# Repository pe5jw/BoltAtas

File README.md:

# BoltATAS

Netwerkcontroller voor de Yaesu **ATAS-100** motorantenne op de FT-897D, op basis van een **WT32-ETH01** (ESP32 + Ethernet).
Meet vooruit- en reflectievermogen (tandem match + 2× AD8307), stuurt de antennemotor via de DC-spanning op de coax
en stemt zelfstandig af op de laagste SWR. Bediening via een HTTP API in BoltSwitch-stijl, of met de knoppen UP, DOWN en TUNE op de print. Drie LED's (groen, oranje, rood) tonen de SWR.

PE5JW — hardware v1.3, firmware v1.2 (2026-11-25)

> **Status:** ontwerp en firmware zijn met tools gecontroleerd, maar er is nog **niets gebouwd of op de band getest**.
> - Schema: één doorverbonden tekening met echte draden. De netlist is door KiCad zelf geëxporteerd en vergeleken met de bedoelde verbindingen (266 pinnen, 60 netten, 0 fouten). Daarbij zijn de pin-types gecontroleerd.
> - PCB: gegenereerd uit dit schema en eraan gekoppeld. DRC geeft 0 fouten en 0 onverbonden pads; er blijven 2 cosmetische silkscreen-waarschuwingen over (WT32-footprint).
> - Firmware: de afstemlogica is getest in een simulatie (9000 runs). De Ethernet/WiFi-wisseling en het frontpaneel (knoppen en SWR-LED's) zijn getest met de echte sketch tegen stubs voor arduino-esp32 core 2.x en 3.x. Met de echte ESP32-toolchain is de sketch hier niet gecompileerd.
>
> Zie [Open punten](#open-punten) voor wat je bij de bouw moet nameten.

## Mappen

| Map | Inhoud |
|---|---|
| `hardware/` | KiCad 7 project: `BoltATAS.kicad_sch`, `.kicad_pcb`, `.kicad_pro`, `.kicad_dru`, projectbibliotheek (`BoltATAS.kicad_sym`, `BoltATAS.pretty/`) |
| `hardware/fab/` | Gerbers + boorbestanden (`BoltATAS-gerbers.zip`), BOM (`BoltATAS-BOM.csv`), bestellijst voor DigiKey (`BoltATAS-BOM-DigiKey.csv`, te uploaden in de BOM Manager), pick&place |
| `hardware/tools/` | Python-generators voor bibliotheek, schema en PCB, netlist-check, DRC, fab-uitvoer (`fab.py`), `build_all.sh` |
| `firmware/BoltATAS/` | Arduino sketch (`BoltATAS.ino`) + platformonafhankelijke logica (`AtasCore.h`) |
| `firmware/test/` | Simulatie van autotune/motor en test van de netwerkwisseling (draait op een PC) |
| `docs/` | Schema als PDF/PNG, PCB-renders, DRC-rapport |

## Hardware

```
FT-897D ─ J1 ─ T1 (stroomtrafo) ─ RF_LINE ─ C1..C3 (DC-blok) ─ RF_ANT ─ J2 ─ ATAS-100
                    │                  │                          │
               FWD_PORT ── T2 (spanningstrafo, 30T naar GND)      L1 RF-choke
                    │      1T tussen FWD_PORT en REF_PORT          │
             13 dB pad → AD8307 → IO36            COAX_DC ← R40 0.1 Ω ← K1/K2 relais ← 12 V / 8 V
             REF: 13 dB pad → AD8307 → IO39             INA180 → IO35 (motorstroom)
```

- **Tandem match** (Sontheimer): twee FT114-43 kernen, 1:30. T1 = stroomtrafo (1 winding = coax-ziel RF_TX→RF_LINE, 30 wdg van GND naar FWD_PORT). T2 = spanningstrafo (30 wdg van RF_LINE naar GND, 1 winding = coax-ziel tussen FWD_PORT en REF_PORT).
- **Koppeling** 29,5 dB + 13 dB π-pad = 42,5 dB. 120 W geeft +8,3 dBm op de AD8307 (lineair tot +16 dBm) en 2,31 V op de ADC; 200 W geeft 2,36 V (ESP32 lineair tot 2,45 V).
- **DC-blok** C1..C3 (3× 100 nF X7R 100 V) ligt tussen koppelaar en bias-tee. Er komt dus geen 8/12 V op de zender, en ook niet op T2 (diens 30 wdg zijn voor DC een kortsluiting).
- **Bias-tee** L1: 20 wdg 0,8 mm CuL op FT114-43 (≈240 µH).
- **Motor:** K1 (12 V = langer = frequentie omlaag) en K2 (8 V = korter = frequentie omhoog). Het NC-contact van K1 voedt de COM van K2, zodat 8 V en 12 V elkaar nooit kunnen raken. In rust ligt de lijn via R41 op 0 V.
- **Motorstroom:** 0,1 Ω + INA180A1 (2 mV/mA) op IO35. Daarmee detecteert de firmware kortsluiting (> 900 mA) en een open lijn (< 10 mA).
- **Frontpaneel** (blok F in het schema, onderrand van de print): knoppen UP, DOWN en TUNE, SWR-LED's groen/oranje/rood, de status-LED en de twee motor-LED's.
  - Knoppen schakelen naar GND, met 10k pull-up en 100 nF (1 ms ontdendering) en 1k in serie naar de GPIO.
  - J5 (1×8) is optioneel, voor knoppen en LED's in een frontplaat: 1 GND, 2 TUNE, 3 DOWN, 4 UP, 5 SWR rood, 6 SWR oranje, 7 SWR groen, 8 STATUS. De knoppen staan parallel aan die op de print. De LED-pinnen zitten ná de serieweerstand: monteer een LED óf op de print óf in de frontplaat, niet allebei.
- **Voeding:** 13,8 V → PTC 1,5 A → SS34 (ompoolbeveiliging) → TVS.
  - LM2940CT-12: low-dropout, want een LM7812 valt bij 13,3 V uit regeling.
  - LM7808.
  - Traco TSR 1-2450: een schakelende 5 V; een LM7805 is pin-compatibel, maar heeft dan een koelplaat nodig.

### Pinnen WT32-ETH01

| GPIO | Functie |
|---|---|
| IO36 | ADC FWD (AD8307 U4) |
| IO39 | ADC REF (AD8307 U5) |
| IO35 | ADC motorstroom |
| IO4 | K1, 12 V, antenne langer |
| IO32 | K2, 8 V, antenne korter |
| IO33 | status-LED |
| IO2 | SWR-LED groen |
| IO12 | SWR-LED oranje |
| IO14 | SWR-LED rood |
| IO15 | knop UP |
| IO5 | knop DOWN |
| IO17 | knop TUNE |
| IO0 | Ethernet-klok (50 MHz). Alleen via R50 naar BOOT-knop/header |

Ethernet gebruikt IO0, 16, 18, 19, 21–23 en 25–27. Daarmee zijn alle vrije GPIO's van de WT32-ETH01 in gebruik.

IO2, IO12, IO5 en IO15 zijn strapping-pinnen. Ze zitten daarom op plekken waar ze het opstarten niet storen:
- IO2 en IO12 sturen een LED naar GND, die houdt ze laag tijdens het booten. IO12 hoog bij het booten zou de flash op 1,8 V zetten.
- IO5 en IO15 zijn ingangen met pull-up; hoog is hun standaardniveau.
- In v1.0 stuurde IO5 een relais aan, dat tijdens het booten kon schakelen. Als knopingang is dat geen probleem.

**Programmeerheader J4** (USB-serieel, 3,3 V): 1 EN, 2 TX, 3 RX, 4 IO0 (via R50), 5 3V3 (alleen referentie, niet voeden), 6 GND. SW2 = RESET, SW1 = BOOT.

### Bouwnotities

1. **Toroids T1/T2:** elke kern staat rechtop in een sleuf in de print, met een stukje RG-58/RG-400 (±60 mm) er recht doorheen.
   - Ziel aan pad A en B. Mantel **aan één kant** solderen (pad SH, kant A); aan de andere kant de mantel afknippen.
   - T2 krijgt de volle lijnspanning: wikkel de 30 windingen met PTFE- of dubbel gelakt draad.
   - De kernen steken ±12 mm onder de print uit, dus gebruik afstandsbussen van ≥ 15 mm.
2. **FWD en REF verwisseld?** Draai de twee draden van de 30 windingen van T1 om.
3. **L1:** meet met een NanoVNA dat |Z| ≥ 1,5 kΩ is over 1,8–30 MHz. Haal je dat niet, voeg dan een tweede choke in serie toe.
4. **Relais:** de pinnummers volgen de KiCad SRD-footprint (1 COM, 3 NO, 4 NC). Controleer vóór het solderen met een multimeter dat COM–NC doorgang heeft.
5. **U1/U2** krijgen een klein koelplaatje, want ze voeren de motorstroom.
6. **WiFi:** de antenne van de WT32-ETH01 zit aan het eind tegenover de RJ45. Daaronder zit geen koper (keep-out). In een metalen kast werkt WiFi nauwelijks; gebruik dan Ethernet of een kunststof deksel.
7. Gerbers staan in `hardware/fab/BoltATAS-gerbers.zip`. Board: 150 × 114 mm, 2 lagen, 1,6 mm. De sleuven zitten in Edge.Cuts.
8. **Frontrij:** de knoppen en LED's staan op één lijn langs de onderrand. Monteer de print zo dat die rand achter de frontplaat zit, of gebruik J5 voor losse knoppen en LED's.

## Firmware

**Bouwen:** Arduino IDE of arduino-cli.
- Board: "WT32-ETH01 Ethernet Module" (of "ESP32 Dev Module").
- Core: arduino-esp32 2.0.x of 3.x.
- Bibliotheek: ArduinoJson 6.21+ of 7.x.

Kopieer `firmware/BoltATAS/secrets.h.example` naar `secrets.h` en vul de WiFi- en OTA-gegevens in.

**Netwerk** (één van beide, nooit allebei):
- Ethernet heeft voorrang.
- WiFi start pas als er na het opstarten 4 s geen kabel is, of 5 s nadat de kabel eruit is getrokken.
- Wordt een kabel ingeplugd, dan gaat WiFi direct uit (al bij link-up, nog vóór DHCP).
- Krijgt Ethernet 20 s lang geen DHCP-adres, dan valt de module terug op WiFi.
- Naam op het netwerk: mDNS `boltatas.local`. OTA-updates werken met wachtwoord.

**Frontpaneel:**
- **UP / DOWN:** de motor draait zolang je de knop vasthoudt (max. 15 s), met of zonder draaggolf. UP en DOWN tegelijk = stop.
- **TUNE:** start de autotune als er een draaggolf van 0,5–25 W is. Nog een keer drukken breekt af.
- Een knop die al ingedrukt is bij het opstarten telt pas na loslaten.
- **Boven 25 W beweegt de motor niet**, ook niet met de knoppen of `/up` en `/down`, omdat de contacten van de spriet dan kunnen vonken. Gaat het vermogen tijdens een handmatige beweging boven 25 W, dan stopt de motor.

**SWR-LED's:**

| LED | Betekenis |
|---|---|
| groen | SWR < 1,5 |
| oranje | SWR 1,5 – 2,5 |
| rood | SWR ≥ 2,5 |
| uit | geen draaggolf (≥ 0,5 W); blijft 0,4 s staan in SSB-pauzes |

De grenzen zijn in te stellen met `/cal?swr_green=1.5&swr_red=2.5`. Er zit 0,05 hysterese op, zodat een LED niet knippert op de grens. Tijdens het afstemmen tonen de LED's de actuele SWR.

De LED's knipperen ook 3× als terugmelding:
- groen: afstemmen gelukt
- oranje: beste resultaat, doel-SWR niet gehaald
- rood: afstemmen mislukt, of TUNE zonder draaggolf
- oranje + rood: vermogen te hoog (> 25 W)

Bij het opstarten branden alle drie kort (lamptest).

**Status-LED:**
- aan: Ethernet
- 1 Hz: WiFi
- 4 Hz: geen netwerk
- 8 Hz: aan het afstemmen
- dubbele flits: motorfout

### HTTP API

Alle verzoeken zijn GET en geven JSON terug, met CORS open.

| Endpoint | Functie |
|---|---|
| `/status` | SWR, FWD/REF in W en dBm, return loss, motorstroom, motorfout, tune-status, netwerk, SWR-LED (`swr_led`), knoppen (`buttons`) |
| `/up` `/down` | Motor draaien tot `/stop`, maximaal 15 s. Boven 25 W: fout 409 `power_too_high` |
| `/up?ms=N` `/down?ms=N` | Motor N ms laten draaien (10…15000) |
| `/stop` | Motor stoppen en lopende afstemming afbreken |
| `/tune` | Autotune starten. Vereist een draaggolf van 0,5–25 W |
| `/tune?target=1.5&dir=up` | Doel-SWR (1.1–3.0) en beginrichting. Gebruik `dir=up` als de frequentie omhoog ging |
| `/cal` | Kalibratie tonen |
| `/cal?fwd_w=10` | FWD-koppeling instellen op een bekend vooruitvermogen (dummy load + referentiemeter) |
| `/cal?ref_w=10` | REF-koppeling instellen: voed hiervoor RF in via de ANT-aansluiting |
| `/cal?travel_ms=45000` | Looptijd van de antenne van eindstop tot eindstop (zelf meten) |
| `/cal?swr_green=1.5&swr_red=2.5` | Grenzen van de SWR-LED's |

`/up` en `/down` breken een lopende autotune af.

**Autotune** werkt in twee fasen:
1. **Sweep:** de motor draait continu en de RF wordt elke 40 ms bemonsterd.
2. **Fijn zoeken:** stapsgewijs, met een halvering van de stapgrootte bij elke omkering. Daarna gaat de antenne terug naar de beste positie.

De firmware **weigert te tunen boven 25 W**, omdat het bewegen van de spriet onder vol vermogen de contacten kan doen vonken. Hij stopt ook bij verlies van RF en bij een motorfout.

## Tests

```bash
cd firmware/test
ARDUINOJSON_SRC=/pad/naar/ArduinoJson/src ./run_tests.sh
```

- **`sim_test`:**
  - RF-rekenwerk, de motor-interlock en de dode tijd tussen relais.
  - Autotune tegen een gesimuleerde ATAS-100, met willekeurige resonantie, startpositie, voetpuntweerstand, coaxverlies, motoruitloop en detectorruis.
  - 3 × 3000 runs: 0 gemist, 0 time-outs.
  - Gemiddeld 40 s zonder richtingshint en 13 s met hint.
- **`sim_test`** test ook het frontpaneel los: ontdendering (ook een knop die vastzit bij het opstarten), de knopacties, en de SWR-kleuren met hysterese, houdtijd en knipperen.
- **`net_test`:** draait de echte sketch tegen stubs met de API van core 2.x en 3.x.
  - Ethernet/WiFi-wisseling: geen kabel, inpluggen, uittrekken, geen DHCP en late DHCP.
  - Frontpaneel: lamptest, UP/DOWN zonder draaggolf, TUNE zonder draaggolf (geweigerd, rood knippert), groen/oranje/rood/uit bij 10 W, UP geweigerd bij 100 W, motor stopt als het vermogen tijdens een beweging boven 25 W komt, TUNE starten en afbreken.

## KiCad-bestanden opnieuw genereren

Het schema en de PCB worden gegenereerd uit `hardware/tools/`. Benodigd: KiCad 7 (`kicad-cli` en de pcbnew-Python-module), Java 25 en `freerouting-2.5.0.jar`.

```bash
FREEROUTING=/pad/freerouting-2.5.0.jar JAVA=java hardware/tools/build_all.sh
```

Dit draait de volgende stappen achter elkaar: bibliotheken → schema → netlist via KiCad → vergelijking met de bedoelde verbindingen → plaatsing → autorouter → GND-vlakken → DRC → Gerbers, BOM, pick&place en de afbeeldingen in `docs/`. Freerouting is niet deterministisch; het script probeert het routeren opnieuw (max. 8×) tot de DRC schoon is.

De footprints in de PCB zijn aan de schemasymbolen gekoppeld, dus **Tools → Update PCB from Schematic** (F8) in KiCad werkt gewoon. Handmatige aanpassingen in KiCad mogen, maar die worden bij een volgende generatorrun overschreven.

## Wijzigingen in v1.3 (hardware) / v1.2 (firmware)

- **Frontpaneel:** knoppen UP, DOWN en TUNE (SW3–SW5) en SWR-LED's groen/oranje/rood (LED4–LED6), met de status-LED en de motor-LED's samen op een rij langs de onderrand. J5 is optioneel, voor een losse frontplaat.
- Print 14 mm hoger: 150 × 114 mm.
- Firmware 1.2.0:
  - knoppen en SWR-LED's;
  - de motor beweegt niet meer boven 25 W, ook niet handmatig;
  - `/status` meldt de SWR-LED en de knoppen;
  - `/cal` heeft de SWR-grenzen erbij.

## Wijzigingen in v1.2

- **Schema opnieuw getekend als één geheel:** alle onderdelen zijn met draden verbonden, met junctions op de aftakkingen. Netlabels staan alleen nog op de belangrijke netten (RF_TX, RF_LINE, FWD_PORT, K1_CTRL, FWD_ADC, enz.) en niet meer op elke pin. Indeling: A RF-pad, B detectoren, C motor/relais, D voeding, E WT32-ETH01. De schakeling zelf is gelijk aan v1.1.
- **J4 PROG** heeft een logischere volgorde: 1 EN, 2 TX, 3 RX, 4 IO0, 5 3V3, 6 GND.
- **PCB opnieuw gegenereerd** uit het nieuwe schema, met de footprints gekoppeld aan de symbolen. Silkscreen opgeschoond: van 12 naar 2 waarschuwingen.
- De generators geven nu steeds dezelfde UUID's, zodat een nieuwe run geen onnodige git-diffs geeft.
- Nieuw: `hardware/tools/fab.py` voor Gerbers, BOM, pick&place en de afbeeldingen.

## Wijzigingen in v1.1 t.o.v. v1.0 (review)

v1.0 had geen bruikbare KiCad-bestanden: het schema bevatte geen draden of symbooldefinities, en de PCB had geen sporen, verkeerde footprints en overlappende onderdelen. De belangrijkste inhoudelijke fouten:

1. **Tandem match:** T2 zat in serie met de lijn in plaats van als spanningstrafo over de lijn. Daardoor was de koppelaar niet richtingsgevoelig en werkte de SWR-meting niet.
2. **DC-blok ontbrak:** de 8/12 V kwam op de antenne-uitgang van de FT-897D.
3. **AD8307 verkeerd aangesloten:**
   - OUT (pin 4) aan GND, ENB (pin 6) als uitgang gebruikt en INM DC aan massa.
   - De 4k7-load verlaagde de slope van 25 naar ±6,8 mV/dB.
   - Een condensator op OFS ontbrak; zonder die condensator ligt de hoogdoorlaatgrens op ±700 kHz.
4. **Overbelasting bij 120 W:** de detector kreeg +21 dBm (max. +16). Opgelost met een 13 dB pad.
5. **Kortsluiting via relais:** het rustcontact van K1 lag aan GND terwijl K2 8 V op hetzelfde punt zette. Nu met hardware-interlock.
6. **RF-choke te klein:** 10 wdg op een FT50-43 is ±52 µH (niet 100 µH) en zit dicht bij verzadiging.
7. **Firmware:**
   - `ETH.begin()` zonder de WT32-instellingen (PHY-adres 1, power GPIO16), waardoor Ethernet niet startte.
   - De tune-loop stopte na één stap.
   - Blocking delays tot 5 s, waardoor `/stop` niet werkte terwijl de motor draaide.
   - Geen afbreken bij verlies van RF.
8. **GPIO5 vervangen door IO32 voor K2:** GPIO5 is een strapping-pin die tijdens het booten schakelt.

## Open punten

- **ATAS-100 spanningen en richting** (8 V korter / 12 V langer) zijn overgenomen uit de projectoverdracht. Controleer dit met de handleiding of een meting aan de FT-897D.
- **Motorstroom van de ATAS:** stel `MOTOR_OPEN_MA` en `MOTOR_SHORT_MA` in de sketch bij na een meting; de waarde is ook af te lezen via `/status`.
- **Looptijd eindstop-tot-eindstop** meten en instellen met `/cal?travel_ms=`.
- **Helderheid van de LED's:** de SWR-LED's krijgen ±4 mA via 330 Ω. Te fel of te zwak? Pas R66–R68 aan.
- **AD8307:** de intercept spreidt enkele dB per exemplaar. Kalibreer met `/cal?fwd_w=` en `/cal?ref_w=`.
- **SRD-relais:** controleer NO/NC (zie bouwnotitie 4).

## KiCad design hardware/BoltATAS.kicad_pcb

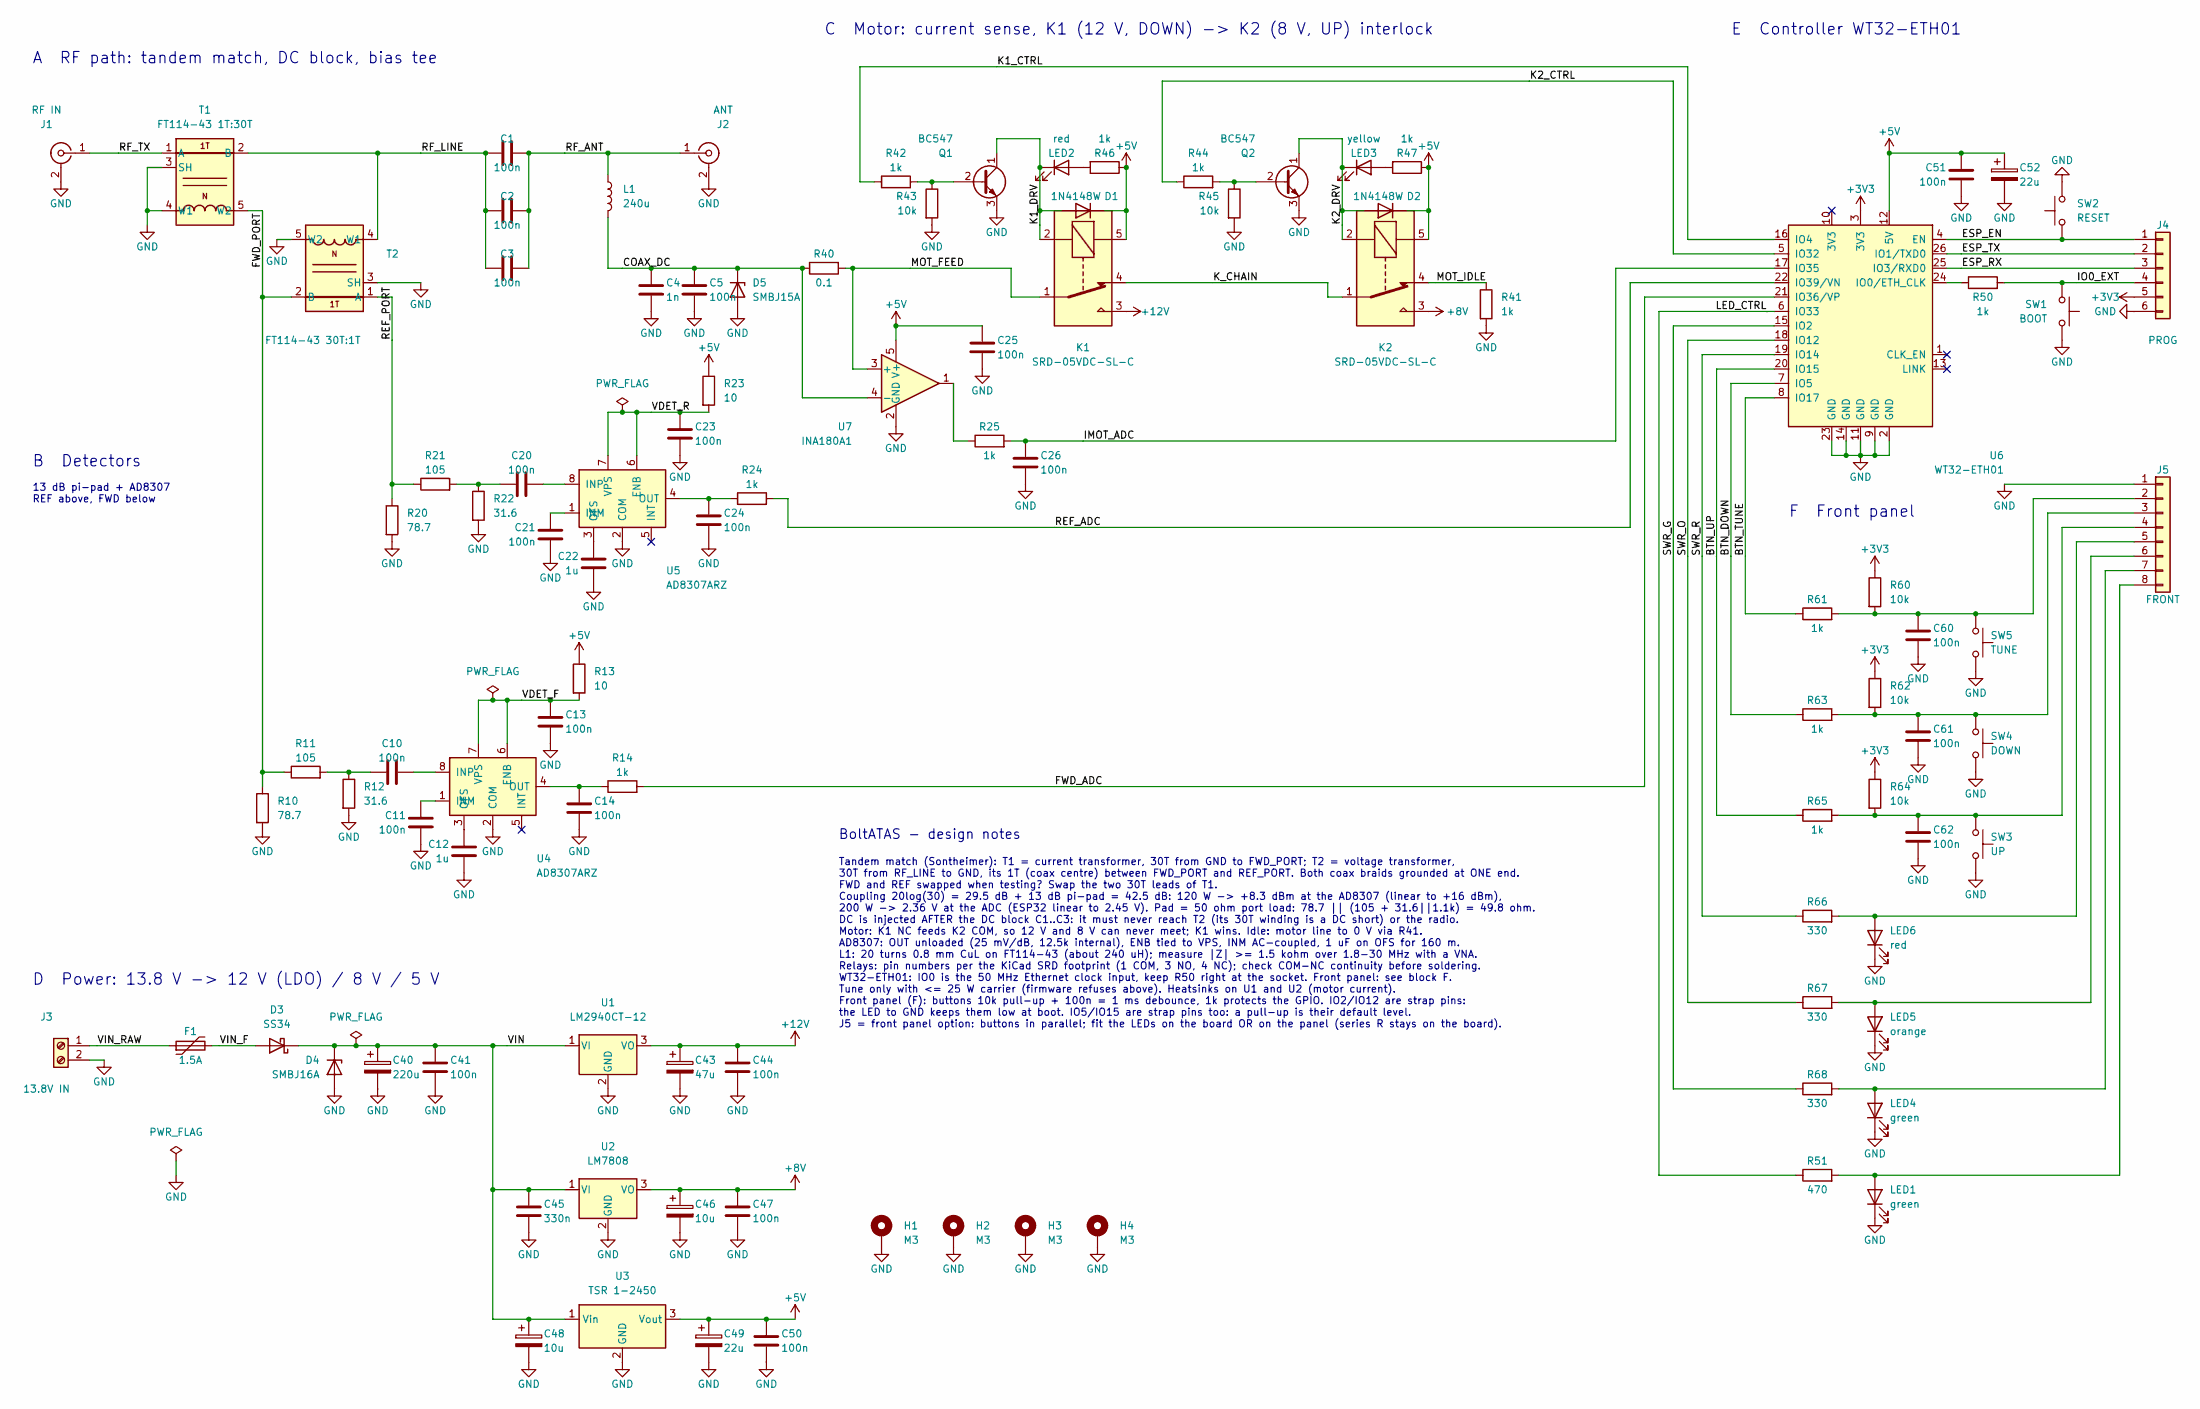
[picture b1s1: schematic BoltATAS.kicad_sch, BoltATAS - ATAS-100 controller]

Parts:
C1, C2, C3: 100n; C_1206_3216Metric
C4: 1n; C_0805_2012Metric
C5, C10, C11, C13, C14, C20, C21, C23, C24, C25, C26, C41, C44, C47, C50, C51, C60, C61, C62: 100n; C_0805_2012Metric
C12, C22: 1u; C_0805_2012Metric
C40: 220u; CP_Radial_D8.0mm_P3.50mm
C43: 47u; CP_Radial_D6.3mm_P2.50mm
C45: 330n; C_0805_2012Metric
C46, C48: 10u; CP_Radial_D6.3mm_P2.50mm
C49, C52: 22u; CP_Radial_D6.3mm_P2.50mm
D1, D2: 1N4148W; D_SOD-123
D3: SS34; D_SMA
D4: SMBJ16A; D_SMB
D5: SMBJ15A; D_SMB
F1: 1.5A; Fuse_1812_4532Metric
H1, H2, H3, H4: M3; MountingHole_3.2mm_M3_Pad_Via
J1: RF IN; Coax_Pigtail
J2: ANT; Coax_Pigtail
J3: 13.8V IN; TerminalBlock_Phoenix_MKDS-1,5-2-5.08_1x02_P5.08mm_Horizont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
J4: PROG; PinHeader_1x06_P2.54mm_Vertical
J5: FRONT; PinHeader_1x08_P2.54mm_Vertical
K1, K2: SRD-05VDC-SL-C; Relay_SPDT_SANYOU_SRD_Series_Form_C
L1: 240u; Toroid_FT114_Flat_Choke
LED1, LED4: green; LED_D3.0mm
LED2, LED6: red; LED_D3.0mm
LED3: yellow; LED_D3.0mm
LED5: orange; LED_D3.0mm
Q1, Q2: BC547; TO-92_Inline_Wide
R10, R20: 78.7; R_2010_5025Metric
R11, R21: 105; R_1206_3216Metric
R12, R22: 31.6; R_0805_2012Metric
R13, R23: 10; R_0805_2012Metric
R14, R24, R25, R41, R42, R44, R46, R47, R50, R61, R63, R65: 1k; R_0805_2012Metric
R40: 0.1; R_2512_6332Metric
R43, R45, R60, R62, R64: 10k; R_0805_2012Metric
R51: 470; R_0805_2012Metric
R66, R67, R68: 330; R_0805_2012Metric
SW1: BOOT; SW_PUSH_6mm
SW2: RESET; SW_PUSH_6mm
SW3: UP; SW_PUSH_6mm
SW4: DOWN; SW_PUSH_6mm
SW5: TUNE; SW_PUSH_6mm
T1: FT114-43 1T:30T; Toroid_FT114_Slot_Coax
T2: FT114-43 30T:1T; Toroid_FT114_Slot_Coax
U1: LM2940CT-12; TO-220-3_Vertical
U2: LM7808; TO-220-3_Vertical
U3: TSR 1-2450; Converter_DCDC_TRACO_TSR-1_THT
U4, U5: AD8307ARZ; SOIC-8_3.9x4.9mm_P1.27mm
U6: WT32-ETH01; WT32-ETH01_Socket
U7: INA180A1; SOT-23-5

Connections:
+3V3: J4.5, R60.1, R62.1, R64.1, U6.3 (3V3)
+5V: C25.1, C49.1, C50.1, C51.1, C52.1, D1.1 (K), D2.1 (K), K1.5, K2.5, R13.1, R23.1, R46.1, R47.1, U3.3 (Vout), U6.12 (5V), U7.5 (V+)
+8V: C46.1, C47.1, K2.3, U2.3 (VO)
+12V: C43.1, C44.1, K1.3, U1.3 (VO)
/BTN_DOWN: R63.1, U6.7 (IO5)
/BTN_TUNE: R61.1, U6.8 (IO17)
/BTN_UP: R65.1, U6.20 (IO15)
/COAX_DC: C4.1, C5.1, D5.1 (K), L1.2, R40.2, U7.4 (-)
/ESP_EN: J4.1, SW2.1, U6.4 (EN)
/ESP_RX: J4.3, U6.25 (IO3/RXD0)
/ESP_TX: J4.2, U6.26 (IO1/TXD0)
/FWD_ADC: R14.2, U6.21 (IO36/VP)
/FWD_PORT: R10.1, R11.1, T1.5 (W2), T2.2 (B)
/IMOT_ADC: C26.1, R25.2, U6.17 (IO35)
/IO0_EXT: J4.4, R50.2, SW1.1
/K1_CTRL: R42.1, U6.16 (IO4)
/K1_DRV: D1.2 (A), K1.2, LED2.1 (K), Q1.1 (C)
/K2_CTRL: R44.1, U6.5 (IO32)
/K2_DRV: D2.2 (A), K2.2, LED3.1 (K), Q2.1 (C)
/K_CHAIN: K1.4, K2.1
/LED_CTRL: R51.1, U6.6 (IO33)
/MOT_FEED: K1.1, R40.1, U7.3 (+)
/MOT_IDLE: K2.4, R41.1
/REF_ADC: R24.2, U6.22 (IO39/VN)
/REF_PORT: R20.1, R21.1, T2.1 (A)
/RF_ANT: C1.2, C2.2, C3.2, J2.1 (In), L1.1
/RF_LINE: C1.1, C2.1, C3.1, T1.2 (B), T2.4 (W1)
/RF_TX: J1.1 (In), T1.1 (A)
/SWR_G: R68.1, U6.15 (IO2)
/SWR_O: R67.1, U6.18 (IO12)
/SWR_R: R66.1, U6.19 (IO14)
/VDET_F: C13.1, R13.2, U4.6 (ENB), U4.7 (VPS)
/VDET_R: C23.1, R23.2, U5.6 (ENB), U5.7 (VPS)
/VIN: C40.1, C41.1, C45.1, C48.1, D3.1 (K), D4.1 (K), U1.1 (VI), U2.1 (VI), U3.1 (Vin)
/VIN_F: D3.2 (A), F1.2
/VIN_RAW: F1.1, J3.1
GND: C4.2, C5.2, C11.2, C12.2, C13.2, C14.2, C21.2, C22.2, C23.2, C24.2, C25.2, C26.2, C40.2, C41.2, C43.2, C44.2, C45.2, C46.2, C47.2, C48.2, C49.2, C50.2, C51.2, C52.2, C60.2, C61.2, C62.2, D4.2 (A), D5.2 (A), H1.1, H2.1, H3.1, H4.1, J1.2 (Ext), J2.2 (Ext), J3.2, J4.6, J5.1, LED1.1 (K), LED4.1 (K), LED5.1 (K), LED6.1 (K), Q1.3 (E), Q2.3 (E), R10.2, R12.2, R20.2, R22.2, R41.2, R43.2, R45.2, SW1.2, SW2.2, SW3.2, SW4.2, SW5.2, T1.3 (SH), T1.4 (W1), T2.3 (SH), T2.5 (W2), U1.2 (GND), U2.2 (GND), U3.2 (GND), U4.2 (COM), U5.2 (COM), U6.2 (GND), U6.9 (GND), U6.11 (GND), U6.14 (GND), U6.23 (GND), U7.2 (GND)
unnamed: C10.1, R11.2, R12.1
unnamed: C20.1, R21.2, R22.1
unnamed: C60.1, J5.2, R60.2, R61.2, SW5.1
unnamed: C61.1, J5.3, R62.2, R63.2, SW4.1
unnamed: C62.1, J5.4, R64.2, R65.2, SW3.1
unnamed: J5.5, LED6.2 (A), R66.2
unnamed: J5.6, LED5.2 (A), R67.2
unnamed: J5.7, LED4.2 (A), R68.2
unnamed: J5.8, LED1.2 (A), R51.2
unnamed: LED2.2 (A), R46.2
unnamed: LED3.2 (A), R47.2
unnamed: Q1.2 (B), R42.2, R43.1
unnamed: Q2.2 (B), R44.2, R45.1
unnamed: R25.1, U7.1
unnamed: C11.1, U4.1 (INM)
unnamed: C10.2, U4.8 (INP)
unnamed: C12.1, U4.3 (OFS)
unnamed: C14.1, R14.1, U4.4 (OUT)
unnamed: C21.1, U5.1 (INM)
unnamed: C20.2, U5.8 (INP)
unnamed: C22.1, U5.3 (OFS)
unnamed: C24.1, R24.1, U5.4 (OUT)
unnamed: R50.1, U6.24 (IO0/ETH_CLK)

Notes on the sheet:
A RF path: tandem match, DC block, bias tee
B Detectors
13 dB pi-pad + AD8307 REF above, FWD below
C Motor: current sense, K1 (12 V, DOWN) -> K2 (8 V, UP) interlock
E Controller WT32-ETH01
F Front panel
D Power: 13.8 V -> 12 V (LDO) / 8 V / 5 V
BoltATAS - design notes
Tandem match (Sontheimer): T1 = current transformer, 30T from GND to FWD_PORT; T2 = voltage transformer, 30T from RF_LINE to GND, its 1T (coax centre) between FWD_PORT and REF_PORT. Both coax braids grounded at ONE end. FWD and REF swapped when testing? Swap the two 30T leads of T1. Coupling 20log(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

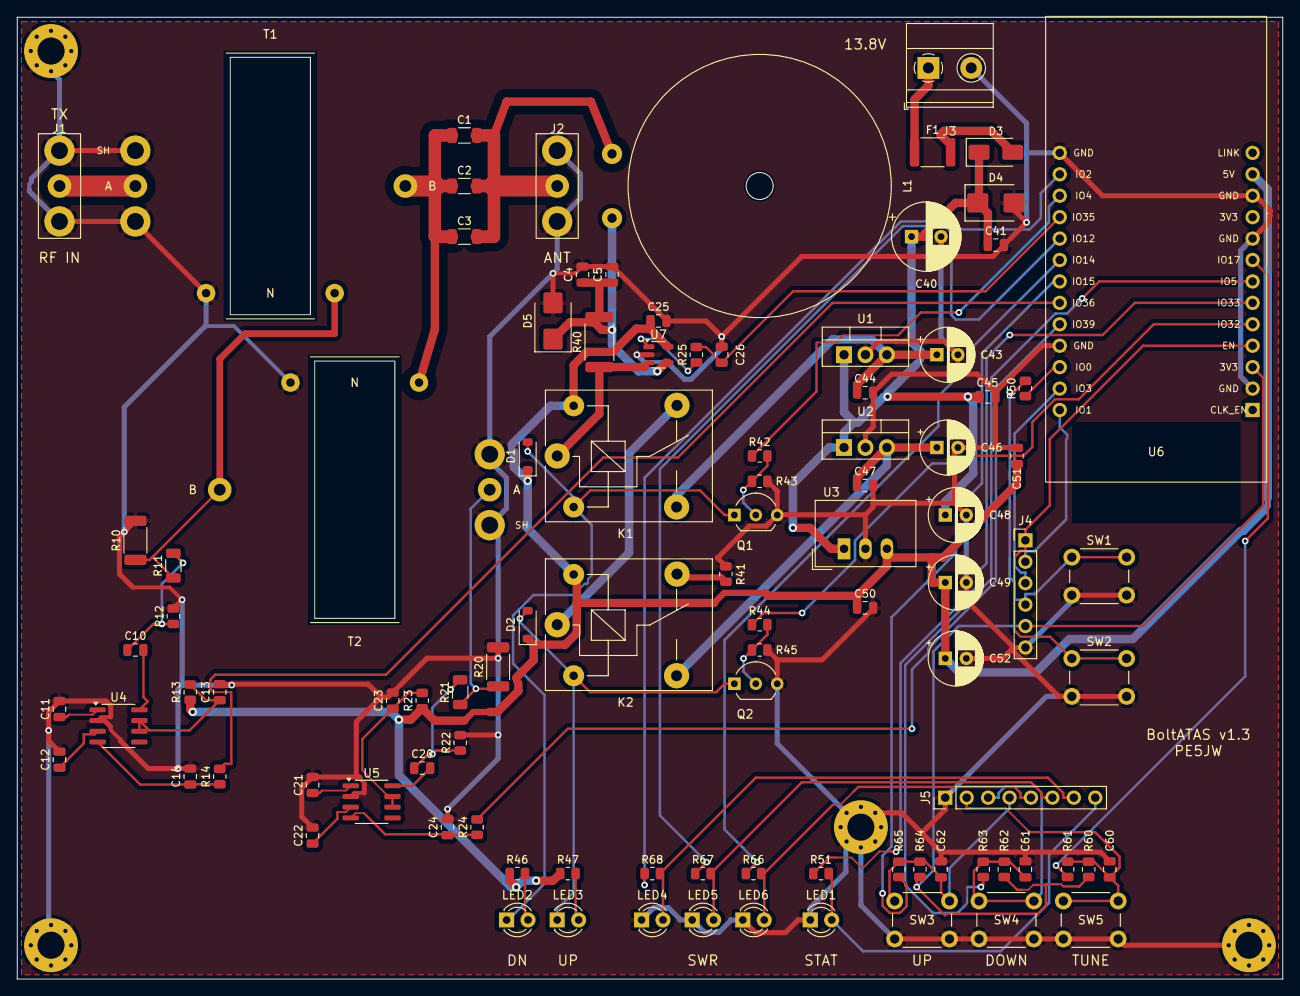
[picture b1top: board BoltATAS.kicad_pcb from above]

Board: 2 copper layers, 150.0 x 114.0 mm, 102 parts (0 on the bottom side), 60 nets.

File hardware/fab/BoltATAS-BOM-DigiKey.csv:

Quantity,Manufacturer Part Number,Customer Reference,Description
1,102991455,U6,WT32-ETH01 (Seeed)
2,61301311821,U6 socket,Female header 1x13 2.54 mm (Wurth)
2,61301311121,U6 pins,Male header 1x13 2.54 mm - only if the WT32 comes without pins
2,AD8307ARZ,U4 U5,Log detector
1,INA180A1IDBVR,U7,Current sense amp 20 V/V
1,LM2940CT-12/NOPB,U1,LDO 12 V TO-220
1,L7808CV,U2,Regulator 8 V TO-220
1,TSR 1-2450,U3,Traco 5 V 1 A switcher
2,577202B00000G,U1 U2,TO-220 heatsink
2,"ORWH-SH-105D1F,000",K1 K2,"Relay 5 V SPDT, DigiKey substitute for Songle SRD-05VDC-SL-C"
2,BC547BTA,Q1 Q2,NPN TO-92
2,1N4148W-7-F,D1 D2,Diode SOD-123
1,SS34-E3/57T,D3,Schottky 3 A SMA
1,SMBJ16A,D4,TVS 16 V SMB
1,SMBJ15A,D5,TVS 15 V SMB
1,1812L150/24MR,F1,PTC 1.5 A 24 V 1812
3,5943001001,L1 T1 T2,Fair-Rite FT114-43 toroid
1,PRT-11363,L1 T1,Magnet wire set 22/26/30 AWG (SparkFun)
1,24PTFESTRGRA25,T2,PTFE wire 24 AWG (may not be at DigiKey)
2,83-1R-RFX,J1 J2,SO-239 panel jack
1,1715721,J3,Terminal block 2p 5.08 mm
1,61300611121,J4,Pin header 1x6
1,61300811121,J5,Pin header 1x8 (optional)
5,B3F-1000,SW1-SW5,Tact switch 6 mm
2,WP710A10GD,LED1 LED4,LED 3 mm green
2,WP710A10ID,LED2 LED6,LED 3 mm red
1,WP710A10YD,LED3,LED 3 mm yellow
1,WP710A10ND,LED5,LED 3 mm orange
3,C1206C104K1RACTU,C1-C3,100n 100V X7R 1206
1,C0805C102J1GACTU,C4,1n 100V C0G 0805
19,CL21B104KBCNNNC,C5 C10 C11 C13 C14 C20 C21 C23 C24 C25 C26 C41 C44 C47 C50 C51 C60 C61 C62,100n 50V X7R 0805
2,CL21B105KBFNNNE,C12 C22,1u 50V X7R 0805
1,CL21B334KBFNNNE,C45,330n 50V X7R 0805
1,EEU-FR1E221,C40,220u 25V 8 mm
1,EEU-FC1E470H,C43,47u 25V 5 mm P2.5
2,EEU-FC1E100H,C46 C48,10u 25V P2.5
2,EEU-FC1C220H,C49 C52,22u 16V P2.5
2,RMCF2010FT78R7,R10 R20,78.7R 1% 0.75W 2010
2,RC1206FR-07105RL,R11 R21,105R 1% 1206
2,RC0805FR-0731R6L,R12 R22,31.6R 1% 0805
2,RC0805FR-0710RL,R13 R23,10R 1% 0805
12,RC0805FR-071KL,R14 R24 R25 R41 R42 R44 R46 R47 R50 R61 R63 R65,1k 1% 0805
5,RC0805FR-0710KL,R43 R45 R60 R62 R64,10k 1% 0805
1,RC0805FR-07470RL,R51,470R 1% 0805
3,RC0805FR-07330RL,R66 R67 R68,330R 1% 0805
1,WSL2512R1000FEA,R40,0.1R 1% 1W 2512

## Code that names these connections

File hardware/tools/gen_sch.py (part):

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      spec="voltage transformer: 30T PTFE/double-enamel wire (full line voltage); 1T = coax centre, braid to SH at end A only",
      refxy=(11.43, -2.54, "left"), valxy=(-3.81, 12.7, None))
for i, ref in enumerate(["C1", "C2", "C3"]):
    place(ref, "Device:C", "100n", C1206, 104.14, 45.72 + 10.16 * i, {"1": "RF_LINE", "2": "RF_ANT"}, rot=90,
          spec="X7R 100V 1206; DC block, 3 in parallel = 0.3 uF")
place("J2", "Connector:Conn_Coaxial", "ANT", "BoltATAS:Coax_Pigtail", 139.7, 45.72, {"1": "RF_ANT", "2": "GND"},
      spec="pigtail RG-58/RG-400 to panel SO-239, to ATAS-100", refxy=(2.54, -5.08, None), valxy=(2.54, -7.62, None))
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k2_in = relay(2, "K2", "Q2", "R44", "R45", "D2", "LED3", "R47", 259.08, "K2_CTRL", "+8V", "MOT_IDLE", "yellow")
PARTS["LED2"]["spec"] = "DOWN / 12 V indicator"
PARTS["LED3"]["spec"] = "UP / 8 V indicator"
PARTS["K1"]["pins"] = {"1": "MOT_FEED", "3": "+12V", "4": "K_CHAIN", "2": "K1_DRV", "5": "+5V"}
PARTS["K2"]["pins"] = {"1": "K_CHAIN", "3": "+8V", "4": "MOT_IDLE", "2": "K2_DRV", "5": "+5V"}
PARTS["K1"]["spec"] = "K1: +12 V = whip longer (DOWN); NC feeds K2 COM = hardware interlock"
PARTS["K2"]["spec"] = "K2: +8 V = whip shorter (UP)"
W("K1.4", (248.92, 68.58), (248.92, 71.12), "K2.1"); LBL("K_CHAIN", (228.6, 68.58))
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place("C51", "Device:C", "100n", C0805, 360.68, 49.53, {"1": "+5V", "2": "GND"},
      refxy=(-2.54, -1.27, "right"), valxy=(-2.54, 1.27, "right"))
place("C52", "Device:C_Polarized", "22u", CP63, 368.3, 49.53, {"1": "+5V", "2": "GND"}, spec="16V")
place("R50", "Device:R", "1k", R0805, 364.49, 68.58, {"1": "ESP_IO0", "2": "IO0_EXT"}, rot=90,
      spec="isolates the 50 MHz Ethernet clock on IO0 from header and button",
      refxy=(0, 2.54, None), valxy=(0, 5.08, None))
place("J4", "Connector_Generic:Conn_01x06", "PROG", "Connector_PinHeader_2.54mm:PinHeader_1x06_P2.54mm_Vertical",
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
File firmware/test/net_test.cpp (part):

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}

static uint8_t swrLedMask() {
  return (g_pin[PIN_SWR_G] ? 1 : 0) | (g_pin[PIN_SWR_O] ? 2 : 0) | (g_pin[PIN_SWR_R] ? 4 : 0);
}

// Run for ms; returns the OR of all SWR LED masks seen and whether a relay was on.
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static void testPanel() {
  bool rel;
  // a. no carrier: UP runs K2 (8 V) while held, release stops
  g_btn[PIN_BTN_UP] = LOW;
  runSeen(300);
  CHECK(g_k2 && !g_k1, "UP held without carrier: K2 on");
  g_btn[PIN_BTN_UP] = HIGH;
  runSeen(100);
  CHECK(!g_k1 && !g_k2, "UP released: motor off");
  // b. DOWN runs K1 (12 V)
  g_btn[PIN_BTN_DOWN] = LOW;
  runSeen(300);
  CHECK(g_k1 && !g_k2, "DOWN held: K1 on");
  g_btn[PIN_BTN_DOWN] = HIGH;
  runSeen(100);
  CHECK(!g_k1 && !g_k2, "DOWN released: motor off");
  printf("t=%5lu UP/DOWN without carrier ok\n", g_ms);
  // c. TUNE without carrier: refused, red flashes, motor stays off
  g_btn[PIN_BTN_TUNE] = LOW;
  uint8_t seen = runSeen(100, &rel);
  g_btn[PIN_BTN_TUNE] = HIGH;
  seen |= runSeen(1000, &rel);
  CHECK(seen == 4 && !rel, "TUNE without carrier: only red flashes, no motor");
  CHECK(!tuner.active(), "no tune without carrier");
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  printf("t=%5lu SWR LEDs green/orange/red/off ok\n", g_ms);
  // e. 100 W: UP refused, orange+red flash
  setRf(100, 1.2f); runSeen(200);
  g_btn[PIN_BTN_UP] = LOW;
  seen = runSeen(300, &rel);
  g_btn[PIN_BTN_UP] = HIGH;
  runSeen(1000);
  CHECK(!rel && (seen & 6) == 6, "UP at 100 W: refused with orange+red flash");
  // f. 10 W: UP runs; power goes to 100 W while held -> stops
  setRf(10, 1.2f); runSeen(600);
  g_btn[PIN_BTN_UP] = LOW;
  runSeen(300);
  CHECK(g_k2, "UP at 10 W: K2 on");
  setRf(100, 1.2f);
  runSeen(150);
  CHECK(!g_k1 && !g_k2, "power above 25 W during a manual move: motor stops");
  g_btn[PIN_BTN_UP] = HIGH;
  setRf(10, 3.0f);
  runSeen(1200);
  // g. TUNE with carrier starts autotune, second press aborts
  g_btn[PIN_BTN_TUNE] = LOW;  runSeen(100);  g_btn[PIN_BTN_TUNE] = HIGH;  runSeen(300);
  CHECK(tuner.active(), "TUNE with 10 W carrier: autotune running");
  g_btn[PIN_BTN_TUNE] = LOW;  runSeen(100);  g_btn[PIN_BTN_TUNE] = HIGH;  runSeen(100);
  CHECK(!tuner.active() && tuner.result() == atas::TuneResult::Aborted, "second TUNE press aborts");
  CHECK(!g_k1 && !g_k2, "motor off after abort");
  printf("t=%5lu buttons with carrier ok\n", g_ms);
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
